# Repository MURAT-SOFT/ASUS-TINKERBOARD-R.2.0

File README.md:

# ASUS-TINKERBOARD-R.2.0
https://learn.microsoft.com/tr-tr/azure/developer/
ASUS TINKERBOARD R.2 AZURE
https://github.com/TinkerBoard-Linux
LINUX KAYNAKLARI
https://www.asus.com/tr/motherboards-components/single-board-computer/all-series/tinker-board/

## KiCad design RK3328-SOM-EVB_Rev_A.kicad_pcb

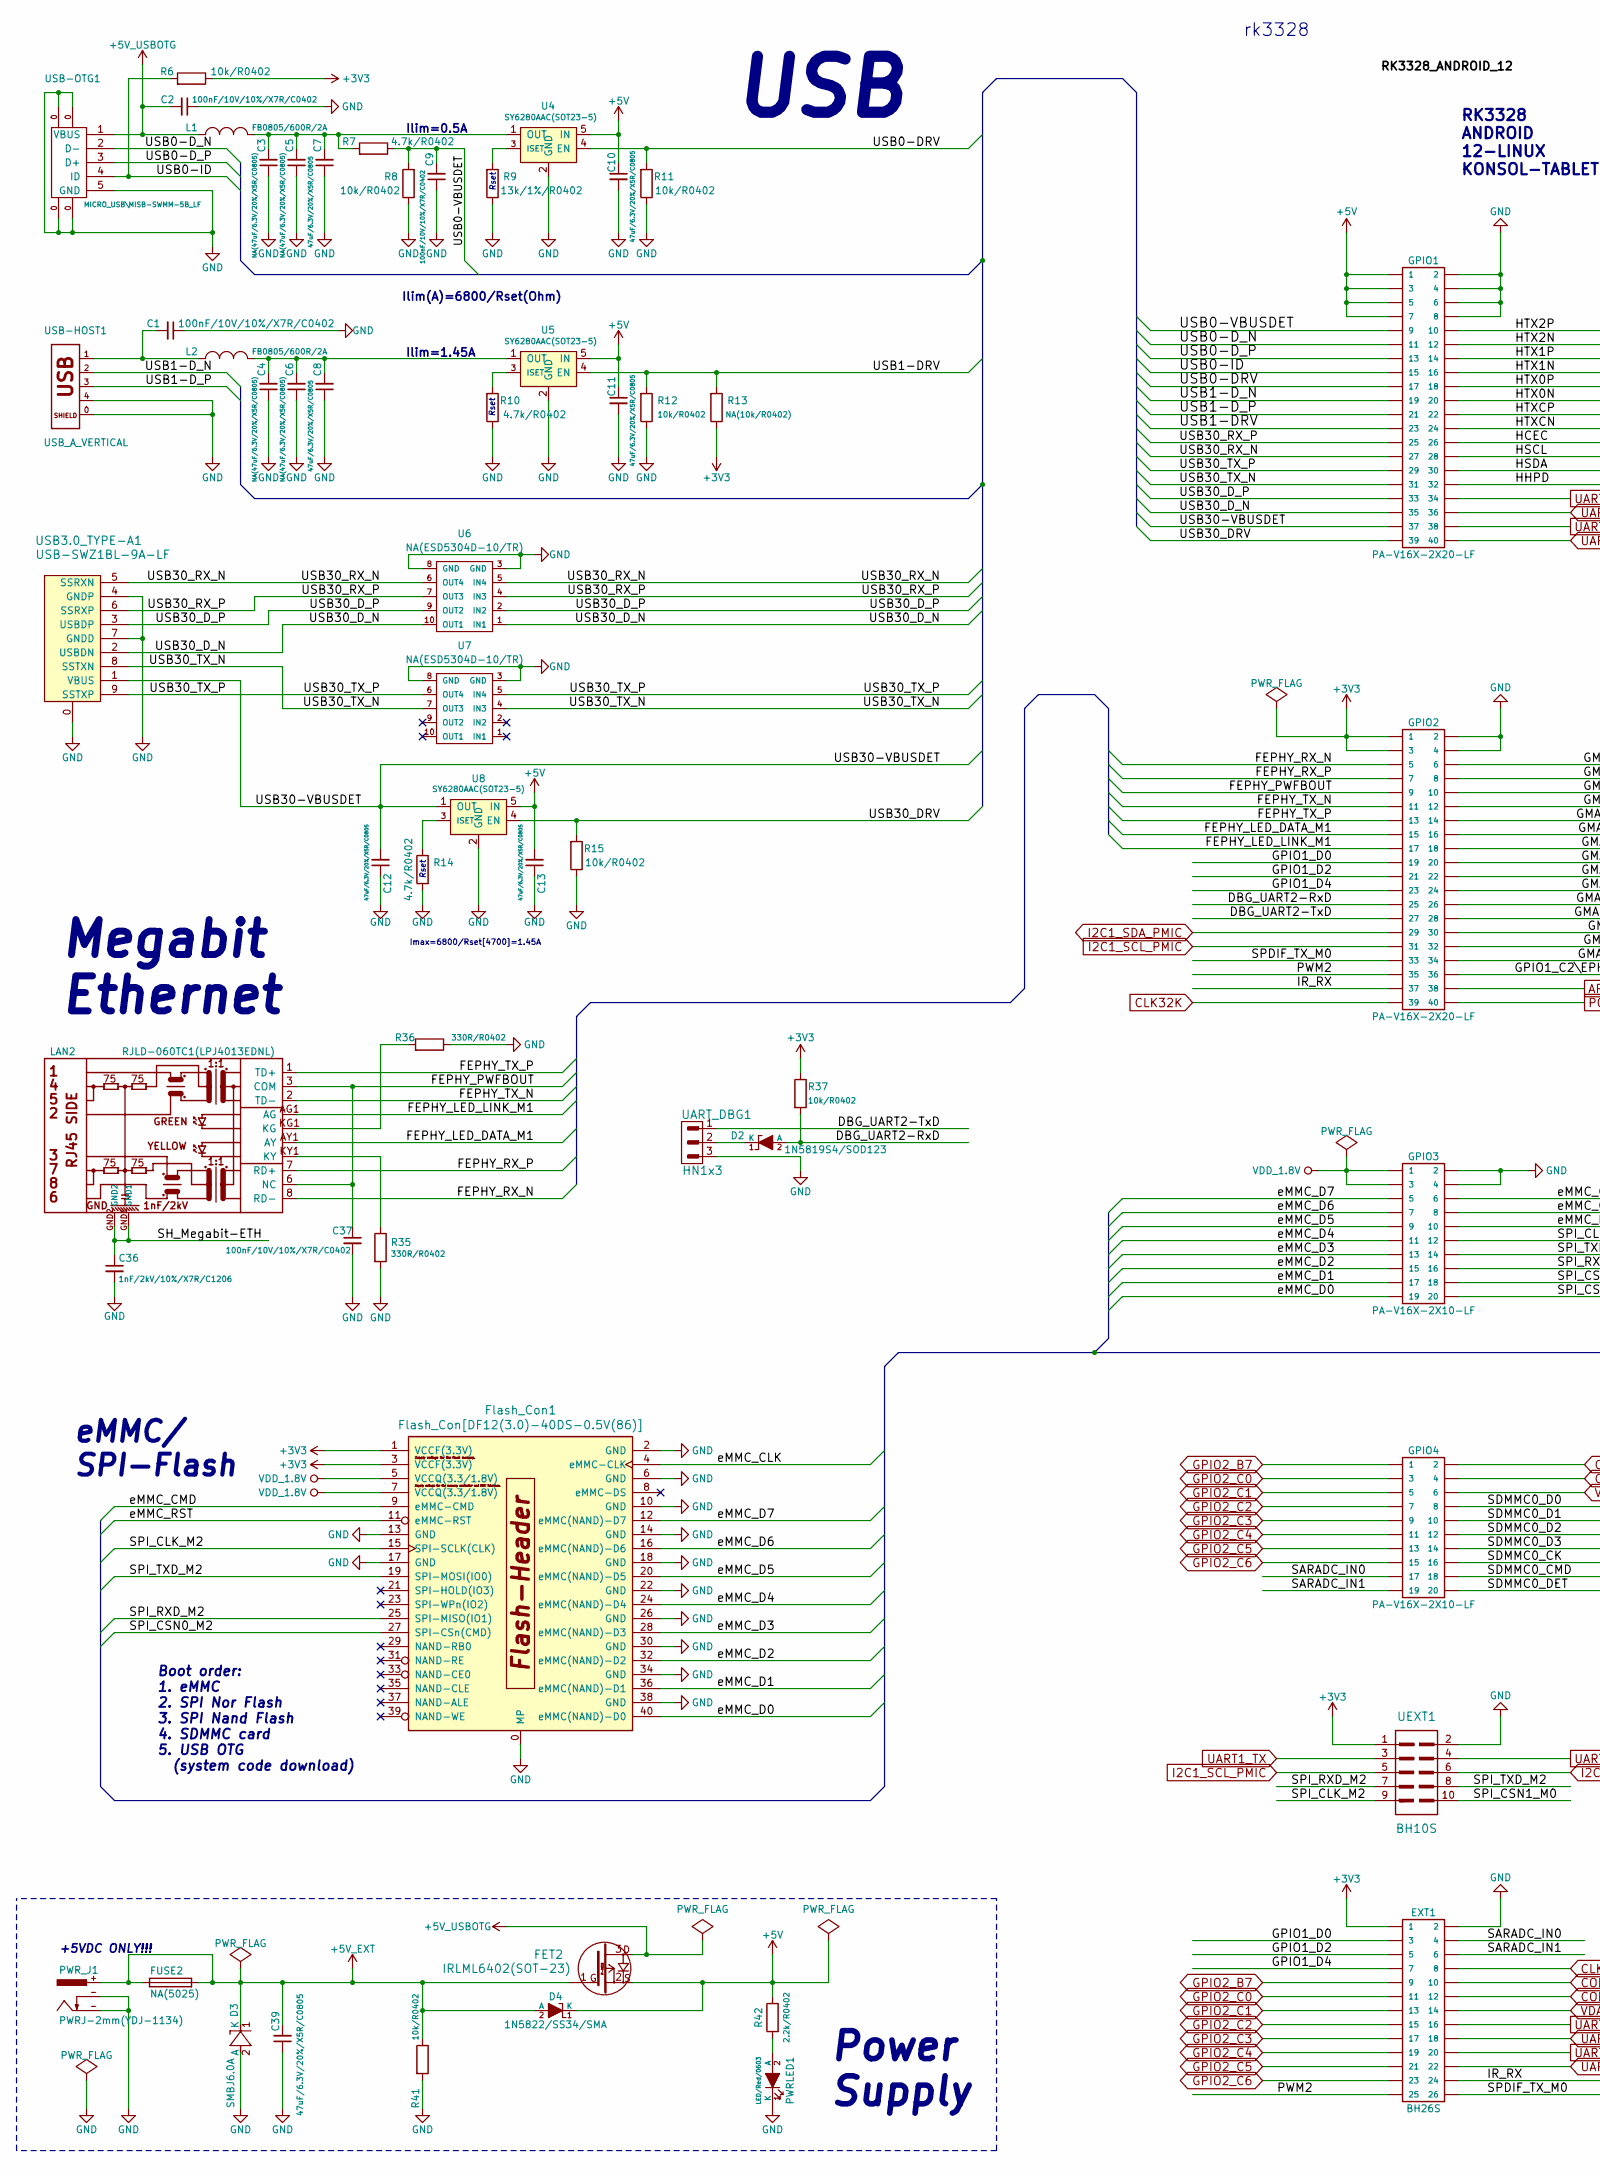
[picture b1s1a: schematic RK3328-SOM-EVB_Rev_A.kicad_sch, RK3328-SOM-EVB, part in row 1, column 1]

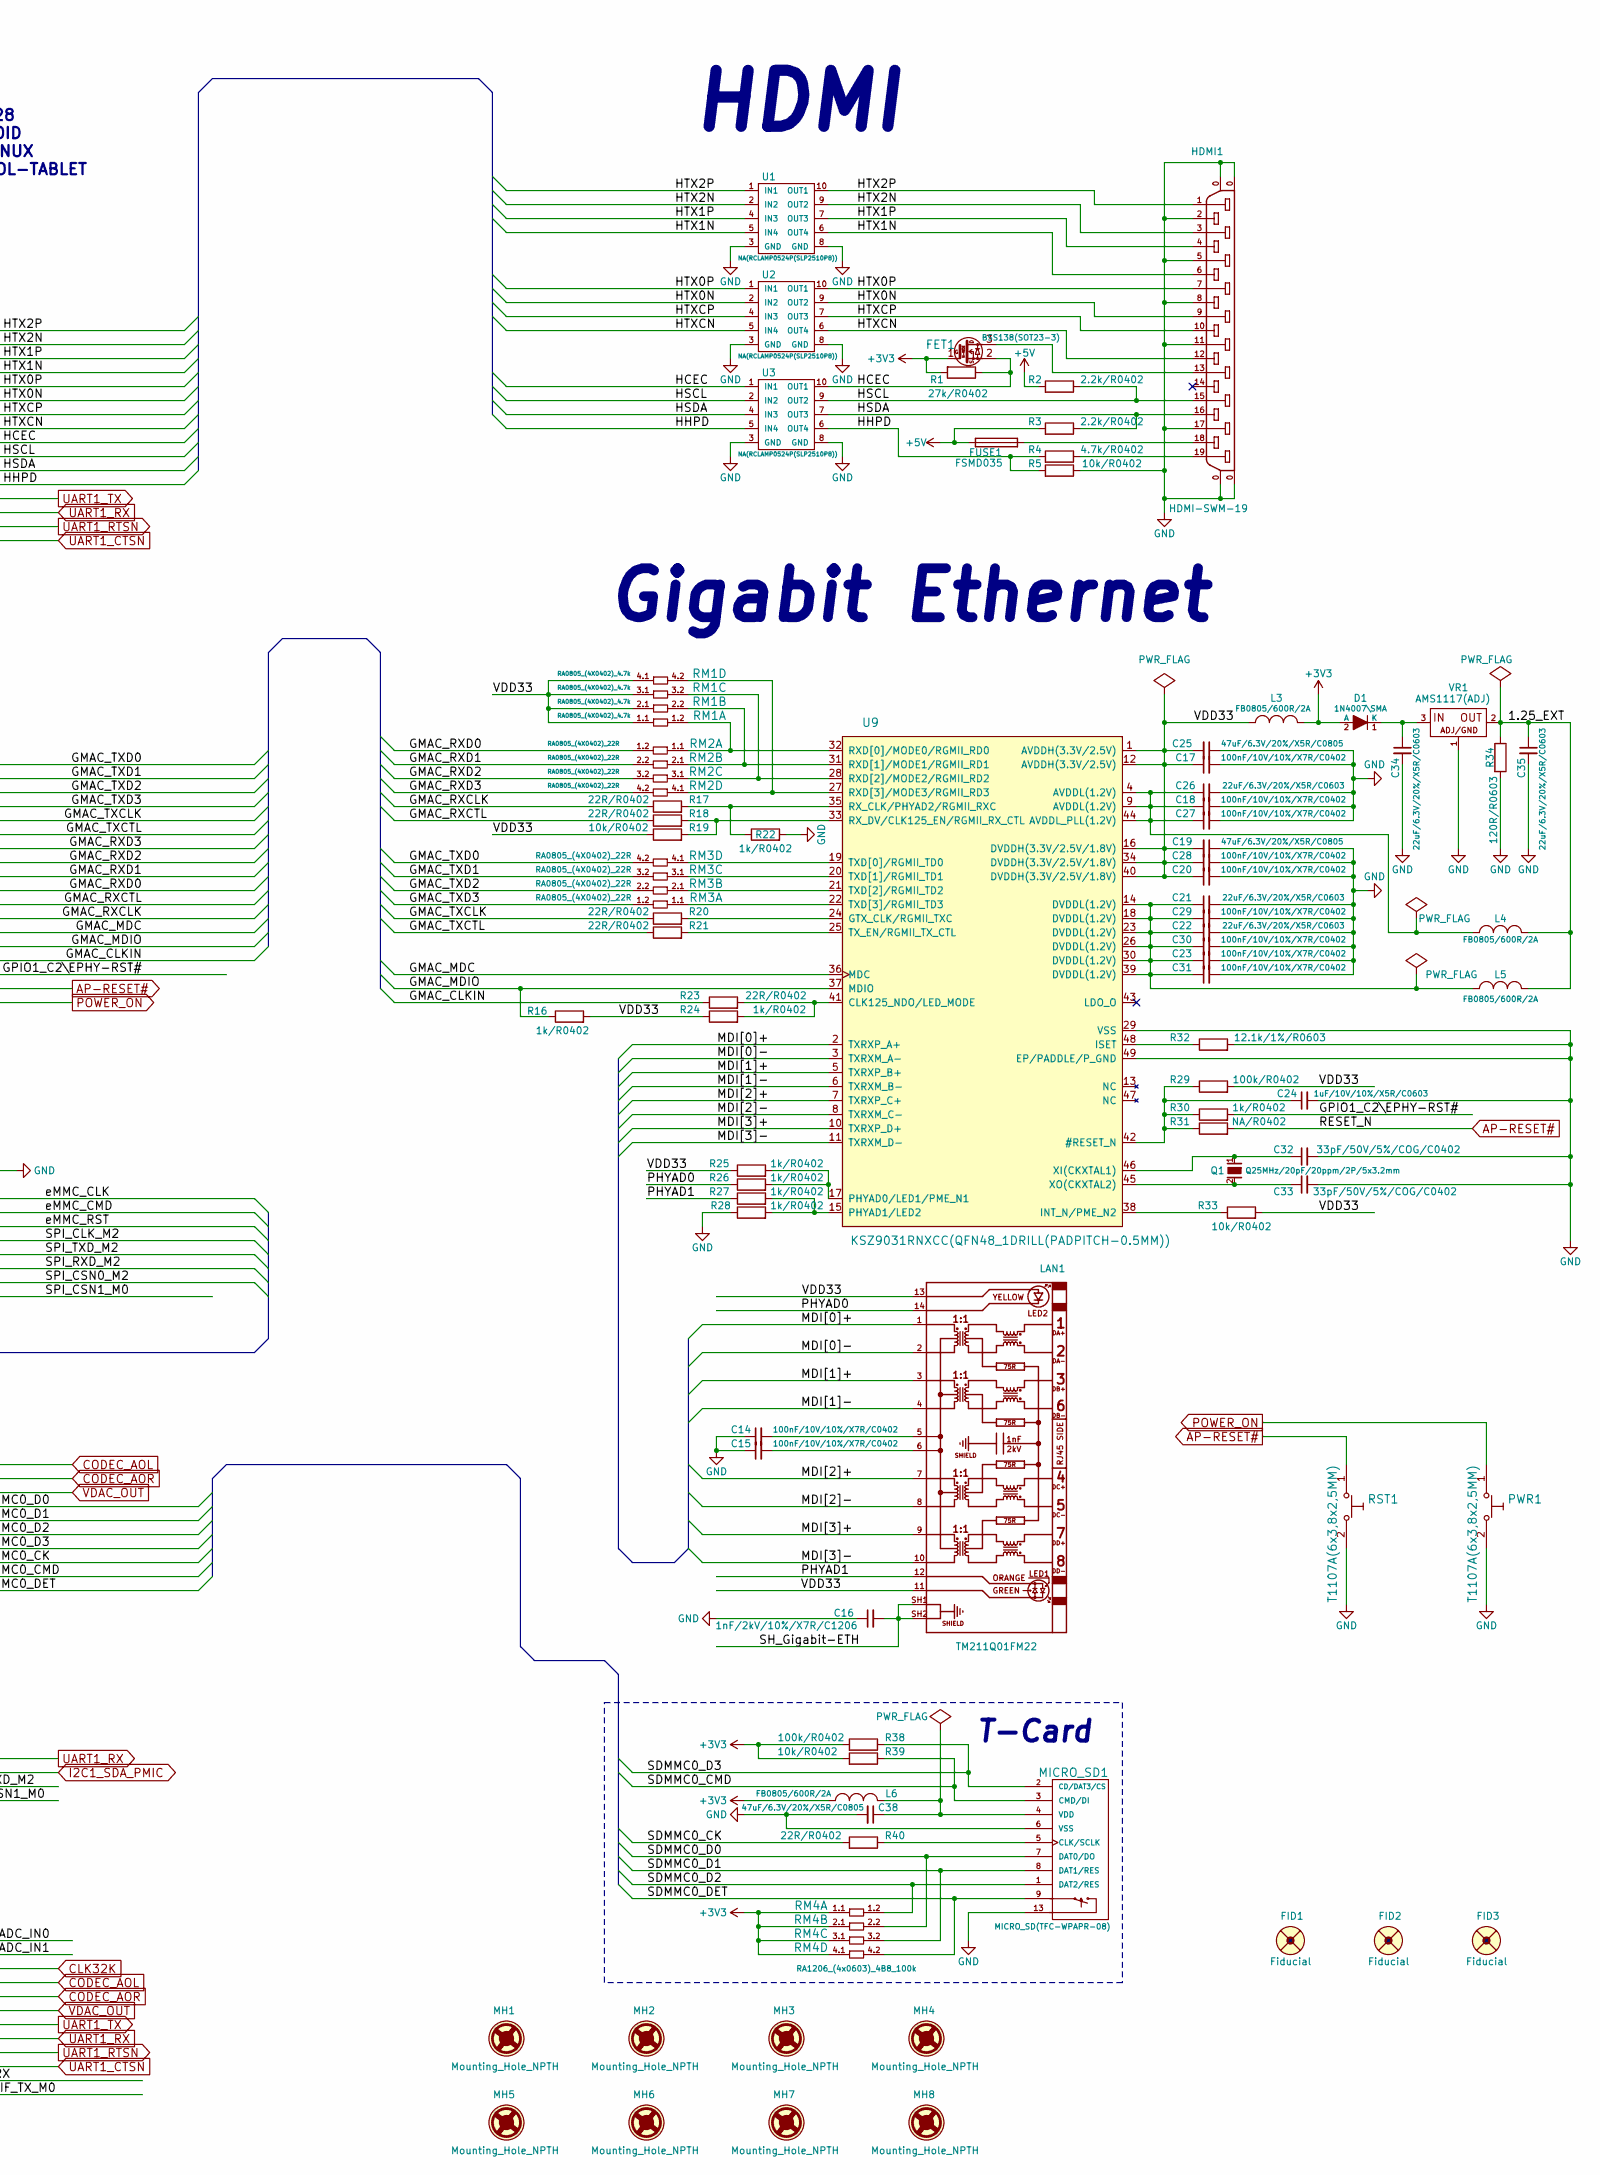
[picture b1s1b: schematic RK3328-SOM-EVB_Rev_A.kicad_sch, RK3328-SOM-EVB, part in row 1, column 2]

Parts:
C1, C2, C9, C14, C15, C17, C18, C20, C23, C27, C28, C29, C30, C31, C37: 100nF/10V/10%/X7R/C0402; C_0402_5MIL_DWS
C3, C4, C5, C6: NA(47uF/6.3V/20%/X5R/C0805); C_0805_5MIL_DWS
C7, C8, C10, C11, C12, C13, C19, C25, C38, C39: 47uF/6.3V/20%/X5R/C0805; C_0805_5MIL_DWS
C16, C36: 1nF/2kV/10%/X7R/C1206; C_1206_5MIL_DWS_ISO
C21, C22, C26, C34, C35: 22uF/6.3V/20%/X5R/C0603; C_0603_5MIL_DWS
C24: 1uF/10V/10%/X5R/C0603; C_0603_5MIL_DWS
C32, C33: 33pF/50V/5%/COG/C0402; C_0402_5MIL_DWS
D1: 1N4007\SMA; SMA-KA
D2: 1N5819S4/SOD123; SOD-123_1C-2A_KA
D3: SMBJ6.0A; DO214AA_1(K)-2(A)
D4: 1N5822/SS34/SMA; SMA-KA
EXT1: BH26S
FET1: BSS138(SOT23-3); SOT23
FET2: IRLML6402(SOT-23); SOT23
FID1, FID2, FID3: Fiducial; Fiducial1x3
FUSE1: FSMD035; FUSE-1206
FUSE2: NA(5025); FUSE-5025
Flash_Con1: Flash_Con[DF12(3.0)-40DS-0.5V(86)]
GPIO1, GPIO2: PA-V16X-2X20-LF; GPH127SMT-02X20(PA-V16X-2X20-LF)
GPIO3, GPIO4: PA-V16X-2X10-LF; GPH127SMT-02X10(PA-V16X-2X10-LF)
HDMI1: HDMI-SWM-19; HDMI-SWM-19-TEST
L1, L2, L3, L4, L5, L6: FB0805/600R/2A; L_0805_5MIL_DWS
LAN1: TM211Q01FM22
LAN2: RJLD-060TC1(LPJ4013EDNL); RJLBC-060TC1
MH1, MH2, MH3, MH4, MH5, MH6, MH7, MH8: Mounting_Hole_NPTH; Mounting_Hole_Drill-3.3mm_Clerance-7mm
MICRO_SD1: MICRO_SD(TFC-WPAPR-08); TFC-WPAPR-08
PWR1: T1107A(6x3,8x2,5MM)
PWRLED1: LED/Red/0603; LED_0603_KA
PWR_J1: PWRJ-2mm(YDJ-1134)
Q1: Q25MHz/20pF/20ppm/2P/5x3.2mm; HCX-4S_2Pins_5.0x3.2mm_TEST
R1: 27k/R0402; R_0402_5MIL_DWS
R2, R3, R42: 2.2k/R0402; R_0402_5MIL_DWS
R4, R7, R10, R14: 4.7k/R0402; R_0402_5MIL_DWS
R5, R6, R8, R11, R12, R15, R19, R33, R37, R39, R41: 10k/R0402; R_0402_5MIL_DWS
R9: 13k/1%/R0402; R_0402_5MIL_DWS
R13: NA(10k/R0402); R_0402_5MIL_DWS
R16, R22, R24, R25, R26, R27, R28, R30: 1k/R0402; R_0402_5MIL_DWS
R17, R18, R20, R21, R23, R40: 22R/R0402; R_0402_5MIL_DWS
R29, R38: 100k/R0402; R_0402_5MIL_DWS
R31: NA/R0402; R_0402_5MIL_DWS
R32: 12.1k/1%/R0603; R_0603_5MIL_DWS
R34: 120R/R0603; R_0603_5MIL_DWS
R35, R36: 330R/R0402; R_0402_5MIL_DWS
RM1: RA0805_(4X0402)_4.7k; RA0805_(4X0402)_xx_BIGGEROUTPADS
RM2, RM3: RA0805_(4X0402)_22R; RA0805_(4X0402)_xx_BIGGEROUTPADS
RM4: RA1206_(4x0603)_4B8_100k; RA1206_(4X0603)_4B8_xx
RST1: T1107A(6x3,8x2,5MM)
U1, U2, U3: NA(RCLAMP0524P(SLP2510P8)); SLP2510P8_TEST
U4, U5, U8: SY6280AAC(SOT23-5); SOT-23-5
U6, U7: NA(ESD5304D-10/TR); SLP2510P8_TEST
U9: KSZ9031RNXCC(QFN48_1DRILL(PADPITCH-0.5MM)); QFN48_1DRILL(PADPITCH-0.5MM)
UART_DBG1: HN1x3
UEXT1: BH10S
USB3.0_TYPE-A1: USB-SWZ1BL-9A-LF; USB3.0-TypeA(USB-SWZ1BL-9A-LF)
USB-HOST1: USB_A_VERTICAL; USB_A_VERTICAL_PTH
USB-OTG1: MICRO_USB\MISB-SWMM-5B_LF; USB-MICRO_MISB-SWMM-5B_LF
VR1: AMS1117(ADJ); SOT223

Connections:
+3V3: D1.2 (A), EXT1.1, FET1.1 (G), Flash_Con1.1 (VCCF(3.3V)), Flash_Con1.3 (VCCF(3.3V)), GPIO2.1, GPIO2.3, L3.2, L6.1, R1.2, R6.1, R13.1, R37.1, R38.2, R39.2, RM4.1.1, RM4.2.1, RM4.3.1, RM4.4.1, UEXT1.1
+5V: C10.1, C11.1, C13.2, D4.1 (K), FET2.2, FUSE1.1, GPIO1.1, GPIO1.3, GPIO1.5, GPIO1.7, R2.2, R3.2, R42.1, U4.5 (IN), U5.5 (IN), U8.5 (IN)
+5V_EXT: C39.2, D3.1 (K), D4.2 (A), FET2.1, FUSE2.1, FUSE2.2, PWR_J1.+, R41.1
+5V_USBOTG: C2.2, FET2.3, L1.1, USB-OTG1.1 (VBUS)
/1.25_EXT: C35.1, L4.2, L5.2, R34.1, VR1.2 (OUT)
/DBG_UART2-RxD: D2.2 (A), GPIO2.25, R37.2
/DBG_UART2-TxD: GPIO2.27, UART_DBG1.1
/FEPHY_LED_DATA_M1: GPIO2.15, LAN2.AY1 (AY)
/FEPHY_LED_LINK_M1: GPIO2.17, LAN2.AG1 (AG)
/FEPHY_PWFBOUT: C37.1, GPIO2.9, LAN2.3 (COM), LAN2.6 (NC)
/FEPHY_RX_N: GPIO2.5, LAN2.8 (RD-)
/FEPHY_RX_P: GPIO2.7, LAN2.7 (RD+)
/FEPHY_TX_N: GPIO2.11, LAN2.2 (TD-)
/FEPHY_TX_P: GPIO2.13, LAN2.1 (TD+)
/GMAC_CLKIN: GPIO2.34, R23.1
/GMAC_MDC: GPIO2.30, U9.36 (MDC)
/GMAC_MDIO: GPIO2.32, R16.1, U9.37 (MDIO)
/GMAC_RXCLK: GPIO2.28, R17.1
/GMAC_RXCTL: GPIO2.26, R18.1
/GMAC_RXD0: GPIO2.24, RM2.1.2
/GMAC_RXD1: GPIO2.22, RM2.2.2
/GMAC_RXD2: GPIO2.20, RM2.3.2
/GMAC_RXD3: GPIO2.18, RM2.4.2
/GMAC_TXCLK: GPIO2.14, R20.1
/GMAC_TXCTL: GPIO2.16, R21.1
/GMAC_TXD0: GPIO2.6, RM3.4.2
/GMAC_TXD1: GPIO2.8, RM3.3.2
/GMAC_TXD2: GPIO2.10, RM3.2.2
/GMAC_TXD3: GPIO2.12, RM3.1.2
/GPIO1_C2\EPHY-RST#: GPIO2.36, R30.2
/GPIO1_D0: EXT1.3, GPIO2.19
/GPIO1_D2: EXT1.5, GPIO2.21
/GPIO1_D4: EXT1.7, GPIO2.23
/HCEC: FET1.2 (S), GPIO1.26, R1.1, U3.1 (IN1), U3.10 (OUT1)
/HHPD: GPIO1.32, R4.2, R5.2, U3.5 (IN4), U3.6 (OUT4)
/HSCL: GPIO1.28, HDMI1.15, R2.1, U3.2 (IN2), U3.9 (OUT2)
/HSDA: GPIO1.30, HDMI1.16, R3.1, U3.4 (IN3), U3.7 (OUT3)
/HTX0N: GPIO1.20, HDMI1.9, U2.2 (IN2), U2.9 (OUT2)
/HTX0P: GPIO1.18, HDMI1.7, U2.1 (IN1), U2.10 (OUT1)
/HTX1N: GPIO1.16, HDMI1.6, U1.5 (IN4), U1.6 (OUT4)
/HTX1P: GPIO1.14, HDMI1.4, U1.4 (IN3), U1.7 (OUT3)
/HTX2N: GPIO1.12, HDMI1.3, U1.2 (IN2), U1.9 (OUT2)
/HTX2P: GPIO1.10, HDMI1.1, U1.1 (IN1), U1.10 (OUT1)
/HTXCN: GPIO1.24, HDMI1.12, U2.5 (IN4), U2.6 (OUT4)
/HTXCP: GPIO1.22, HDMI1.10, U2.4 (IN3), U2.7 (OUT3)
/IR_RX: EXT1.24, GPIO2.37
/MDI[0]+: LAN1.1, U9.2 (TXRXP_A+)
/MDI[0]-: LAN1.2, U9.3 (TXRXM_A-)
/MDI[1]+: LAN1.3, U9.5 (TXRXP_B+)
/MDI[1]-: LAN1.4, U9.6 (TXRXM_B-)
/MDI[2]+: LAN1.7, U9.7 (TXRXP_C+)
/MDI[2]-: LAN1.8, U9.8 (TXRXM_C-)
/MDI[3]+: LAN1.9, U9.10 (TXRXP_D+)
/MDI[3]-: LAN1.10, U9.11 (TXRXM_D-)
/PHYAD0: LAN1.14, R26.1
/PHYAD1: LAN1.12, R27.1
/PWM2: EXT1.25, GPIO2.35
/SARADC_IN0: EXT1.4, GPIO4.17
/SARADC_IN1: EXT1.6, GPIO4.19
/SDMMC0_CK: GPIO4.16, R40.2
/SDMMC0_CMD: GPIO4.18, MICRO_SD1.3 (CMD/DI), R39.1
/SDMMC0_D0: GPIO4.8, MICRO_SD1.7 (DAT0/DO), RM4.2.2
/SDMMC0_D1: GPIO4.10, MICRO_SD1.8 (DAT1/RES), RM4.3.2
/SDMMC0_D2: GPIO4.12, MICRO_SD1.1 (DAT2/RES), RM4.1.2
/SDMMC0_D3: GPIO4.14, MICRO_SD1.2 (CD/DAT3/CS), R38.1
/SDMMC0_DET: GPIO4.20, MICRO_SD1.9, RM4.4.2
/SH_Gigabit-ETH: C16.2, LAN1.SH1, LAN1.SH2
/SH_Megabit-ETH: C36.1, LAN2.GND1, LAN2.GND2
/SPDIF_TX_M0: EXT1.26, GPIO2.33
/SPI_CLK_M2: Flash_Con1.15 (SPI-SCLK(CLK)), GPIO3.12, UEXT1.9
/SPI_CSN0_M2: Flash_Con1.27 (SPI-CSn(CMD)), GPIO3.18
/SPI_CSN1_M0: GPIO3.20, UEXT1.10
/SPI_RXD_M2: Flash_Con1.25 (SPI-MISO(IO1)), GPIO3.16, UEXT1.7
/SPI_TXD_M2: Flash_Con1.19 (SPI-MOSI(IO0)), GPIO3.14, UEXT1.8
/USB0-DRV: GPIO1.17, R11.2, U4.4 (EN)
/USB0-D_N: GPIO1.11, USB-OTG1.2 (D-)
/USB0-D_P: GPIO1.13, USB-OTG1.3 (D+)
/USB0-ID: GPIO1.15, R6.2, USB-OTG1.4 (ID)
/USB0-VBUSDET: C9.2, GPIO1.9, R7.1, R8.2
/USB1-DRV: GPIO1.23, R12.2, R13.2, U5.4 (EN)
/USB1-D_N: GPIO1.19, USB-HOST1.2
/USB1-D_P: GPIO1.21, USB-HOST1.3
/USB30-VBUSDET: C12.2, GPIO1.37, U8.1 (OUT), USB3.0_TYPE-A1.1 (VBUS)
/USB30_DRV: GPIO1.39, R15.2, U8.4 (EN)
/USB30_D_N: GPIO1.35, U6.1 (IN1), U6.10 (OUT1), USB3.0_TYPE-A1.2 (USBDN)
/USB30_D_P: GPIO1.33, U6.2 (IN2), U6.9 (OUT2), USB3.0_TYPE-A1.3 (USBDP)
/USB30_RX_N: GPIO1.27, U6.5 (IN4), U6.6 (OUT4), USB3.0_TYPE-A1.5 (SSRXN)
/USB30_RX_P: GPIO1.25, U6.4 (IN3), U6.7 (OUT3), USB3.0_TYPE-A1.6 (SSRXP)
/USB30_TX_N: GPIO1.31, U7.4 (IN3), U7.7 (OUT3), USB3.0_TYPE-A1.8 (SSTXN)
/USB30_TX_P: GPIO1.29, U7.5 (IN4), U7.6 (OUT4), USB3.0_TYPE-A1.9 (SSTXP)
/VDD33: C17.1, C19.2, C20.1, C25.2, C28.1, L3.1, LAN1.11, LAN1.13, R16.2, R19.1, R24.1, R25.1, R29.2, R33.2, RM1.1.1, RM1.2.1, RM1.3.1, RM1.4.1, U9.1 (AVDDH(3.3V/2.5V)), U9.12 (AVDDH(3.3V/2.5V)), U9.16 (DVDDH(3.3V/2.5V/1.8V)), U9.34 (DVDDH(3.3V/2.5V/1.8V)), U9.40 (DVDDH(3.3V/2.5V/1.8V))
/eMMC_CLK: Flash_Con1.4 (eMMC-CLK), GPIO3.6
/eMMC_CMD: Flash_Con1.9 (eMMC-CMD), GPIO3.8
/eMMC_D0: Flash_Con1.40 (eMMC(NAND)-D0), GPIO3.19
/eMMC_D1: Flash_Con1.36 (eMMC(NAND)-D1), GPIO3.17
/eMMC_D2: Flash_Con1.32 (eMMC(NAND)-D2), GPIO3.15
/eMMC_D3: Flash_Con1.28 (eMMC(NAND)-D3), GPIO3.13
/eMMC_D4: Flash_Con1.24 (eMMC(NAND)-D4), GPIO3.11
/eMMC_D5: Flash_Con1.20 (eMMC(NAND)-D5), GPIO3.9
/eMMC_D6: Flash_Con1.16 (eMMC(NAND)-D6), GPIO3.7
/eMMC_D7: Flash_Con1.12 (eMMC(NAND)-D7), GPIO3.5
/eMMC_RST: Flash_Con1.11 (eMMC-RST), GPIO3.10
AP-RESET#: GPIO2.38, R31.2, RST1.1
CLK32K: EXT1.8, GPIO2.39
CODEC_AOL: EXT1.10, GPIO4.2
CODEC_AOR: EXT1.12, GPIO4.4
GND: C1.1, C2.1, C3.1, C4.1, C5.1, C6.1, C7.1, C8.1, C9.1, C10.2, C11.2, C12.1, C13.1, C14.1, C15.1, C16.1, C17.2, C18.2, C19.1, C20.2, C21.2, C22.2, C23.2, C24.2, C25.1, C26.2, C27.2, C28.2, C29.2, C30.2, C31.2, C32.2, C33.2, C34.2, C35.2, C36.2, C37.2, C38.2, C39.1, D3.2 (A), EXT1.2, Flash_Con1.0 (MP), Flash_Con1.2 (GND), Flash_Con1.6 (GND), Flash_Con1.10 (GND), Flash_Con1.13 (GND), Flash_Con1.14 (GND), Flash_Con1.17 (GND), Flash_Con1.18 (GND), Flash_Con1.22 (GND), Flash_Con1.26 (GND), Flash_Con1.30 (GND), Flash_Con1.34 (GND), Flash_Con1.38 (GND), GPIO1.2, GPIO1.4, GPIO1.6, GPIO1.8, GPIO2.2, GPIO2.4, GPIO3.2, GPIO3.4, HDMI1.0 (20), HDMI1.2, HDMI1.5, HDMI1.8, HDMI1.11, HDMI1.17, MICRO_SD1.6 (VSS), MICRO_SD1.10, MICRO_SD1.11, MICRO_SD1.12, MICRO_SD1.13, PWR1.2, PWRLED1.1 (K), PWR_J1.-, R5.1, R8.1, R9.1, R10.1, R11.1, R12.1, R14.2, R15.1, R22.2, R28.1, R32.2, R34.2, R35.2, R36.1, R41.2, RST1.2, U1.3 (GND), U1.8 (GND), U2.3 (GND), U2.8 (GND), U3.3 (GND), U3.8 (GND), U4.2 (GND), U5.2 (GND), U6.3 (GND), U6.8 (GND), U7.3 (GND), U7.8 (GND), U8.2 (GND), U9.29 (VSS), U9.49 (EP/PADDLE/P_GND), UART_DBG1.3, UEXT1.2, USB3.0_TYPE-A1.0, USB3.0_TYPE-A1.4 (GNDP), USB3.0_TYPE-A1.7 (GNDD), USB-HOST1.0 (5), USB-HOST1.4, USB-OTG1.0, USB-OTG1.5 (GND), VR1.1 (ADJ/GND)
GPIO2_B7: EXT1.9, GPIO4.1
GPIO2_C0: EXT1.11, GPIO4.3
GPIO2_C1: EXT1.13, GPIO4.5
GPIO2_C2: EXT1.15, GPIO4.7
GPIO2_C3: EXT1.17, GPIO4.9
GPIO2_C4: EXT1.19, GPIO4.11
GPIO2_C5: EXT1.21, GPIO4.13
GPIO2_C6: EXT1.23, GPIO4.15
I2C1_SCL_PMIC: GPIO2.31, UEXT1.5
I2C1_SDA_PMIC: GPIO2.29, UEXT1.6
unnamed: C1.2, L2.1, USB-HOST1.1
unnamed: C3.2, C5.2, C7.2, L1.2, R7.2, U4.1 (OUT)
unnamed: C4.2, C6.2, C8.2, L2.2, U5.1 (OUT)
unnamed: C14.2, LAN1.5
unnamed: C15.2, LAN1.6
unnamed: C18.1, C26.1, C27.1, L4.1, U9.4 (AVDDL(1.2V)), U9.9 (AVDDL(1.2V)), U9.44 (AVDDL_PLL(1.2V))
unnamed: C21.1, C22.1, C23.1, C29.1, C30.1, C31.1, L5.1, U9.14 (DVDDL(1.2V)), U9.18 (DVDDL(1.2V)), U9.23 (DVDDL(1.2V)), U9.26 (DVDDL(1.2V)), U9.30 (DVDDL(1.2V)), U9.39 (DVDDL(1.2V))
unnamed: C24.1, R29.1, R30.1, R31.1, U9.42 (#RESET_N)
unnamed: C32.1, Q1.1, U9.46 (XI(CKXTAL1))
unnamed: C33.1, Q1.2, U9.45 (XO(CKXTAL2))
unnamed: C34.1, D1.1 (K), VR1.3 (IN)
unnamed: C38.1, L6.2, MICRO_SD1.4 (VDD)
unnamed: D2.1 (K), UART_DBG1.2
unnamed: FET1.3 (D), HDMI1.13
unnamed: FUSE1.2, HDMI1.18
unnamed: HDMI1.19, R4.1
unnamed: LAN2.KG1 (KG), R36.2
unnamed: LAN2.KY1 (KY), R35.1
unnamed: MICRO_SD1.5 (CLK/SCLK), R40.1
unnamed: PWRLED1.2 (A), R42.2
unnamed: R9.2, U4.3 (ISET)
unnamed: R10.2, U5.3 (ISET)
unnamed: R14.1, U8.3 (ISET)
unnamed: R17.2, R22.1, U9.35 (RX_CLK/PHYAD2/RGMII_RXC)
unnamed: R18.2, R19.2, U9.33 (RX_DV/CLK125_EN/RGMII_RX_CTL)
unnamed: R20.2, U9.24 (GTX_CLK/RGMII_TXC)
unnamed: R21.2, U9.25 (TX_EN/RGMII_TX_CTL)
unnamed: R23.2, R24.2, U9.41 (CLK125_NDO/LED_MODE)
unnamed: R25.2, R26.2, U9.17 (PHYAD0/LED1/PME_N1)
unnamed: R27.2, R28.2, U9.15 (PHYAD1/LED2)
unnamed: R32.1, U9.48 (ISET)
unnamed: R33.1, U9.38 (INT_N/PME_N2)
unnamed: RM1.1.2, RM2.1.1, U9.32 (RXD[0]/MODE0/RGMII_RD0)
unnamed: RM1.2.2, RM2.2.1, U9.31 (RXD[1]/MODE1/RGMII_RD1)
unnamed: RM1.3.2, RM2.3.1, U9.28 (RXD[2]/MODE2/RGMII_RD2)
unnamed: RM1.4.2, RM2.4.1, U9.27 (RXD[3]/MODE3/RGMII_RD3)
unnamed: RM3.1.1, U9.22 (TXD[3]/RGMII_TD3)
unnamed: RM3.2.1, U9.21 (TXD[2]/RGMII_TD2)
unnamed: RM3.3.1, U9.20 (TXD[1]/RGMII_TD1)
unnamed: RM3.4.1, U9.19 (TXD[0]/RGMII_TD0)
POWER_ON: GPIO2.40, PWR1.1
UART1_CTSN: EXT1.22, GPIO1.40
UART1_RTSN: EXT1.20, GPIO1.38
UART1_RX: EXT1.18, GPIO1.36, UEXT1.4
UART1_TX: EXT1.16, GPIO1.34, UEXT1.3
VDAC_OUT: EXT1.14, GPIO4.6
VDD_1.8V: Flash_Con1.5 (VCCQ(3.3/1.8V)), Flash_Con1.7 (VCCQ(3.3/1.8V)), GPIO3.1, GPIO3.3

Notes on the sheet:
RK3328 ANDROID 12-LINUX KONSOL-TABLET
HDMI
Ilim(A)=6800/Rset(Ohm)
+5VDC ONLY!!!
Ilim=1.45A
Power Supply
Gigabit Ethernet
Rset
Megabit Ethernet
rk3328
eMMC/ SPI-Flash
T-Card
Imax=6800/Rset[4700]=1.45A
USB
Boot order: 1. eMMC 2. SPI Nor Flash 3. SPI Nand Flash 4. SDMMC card 5. USB OTG (system code download)
Ilim=0.5A

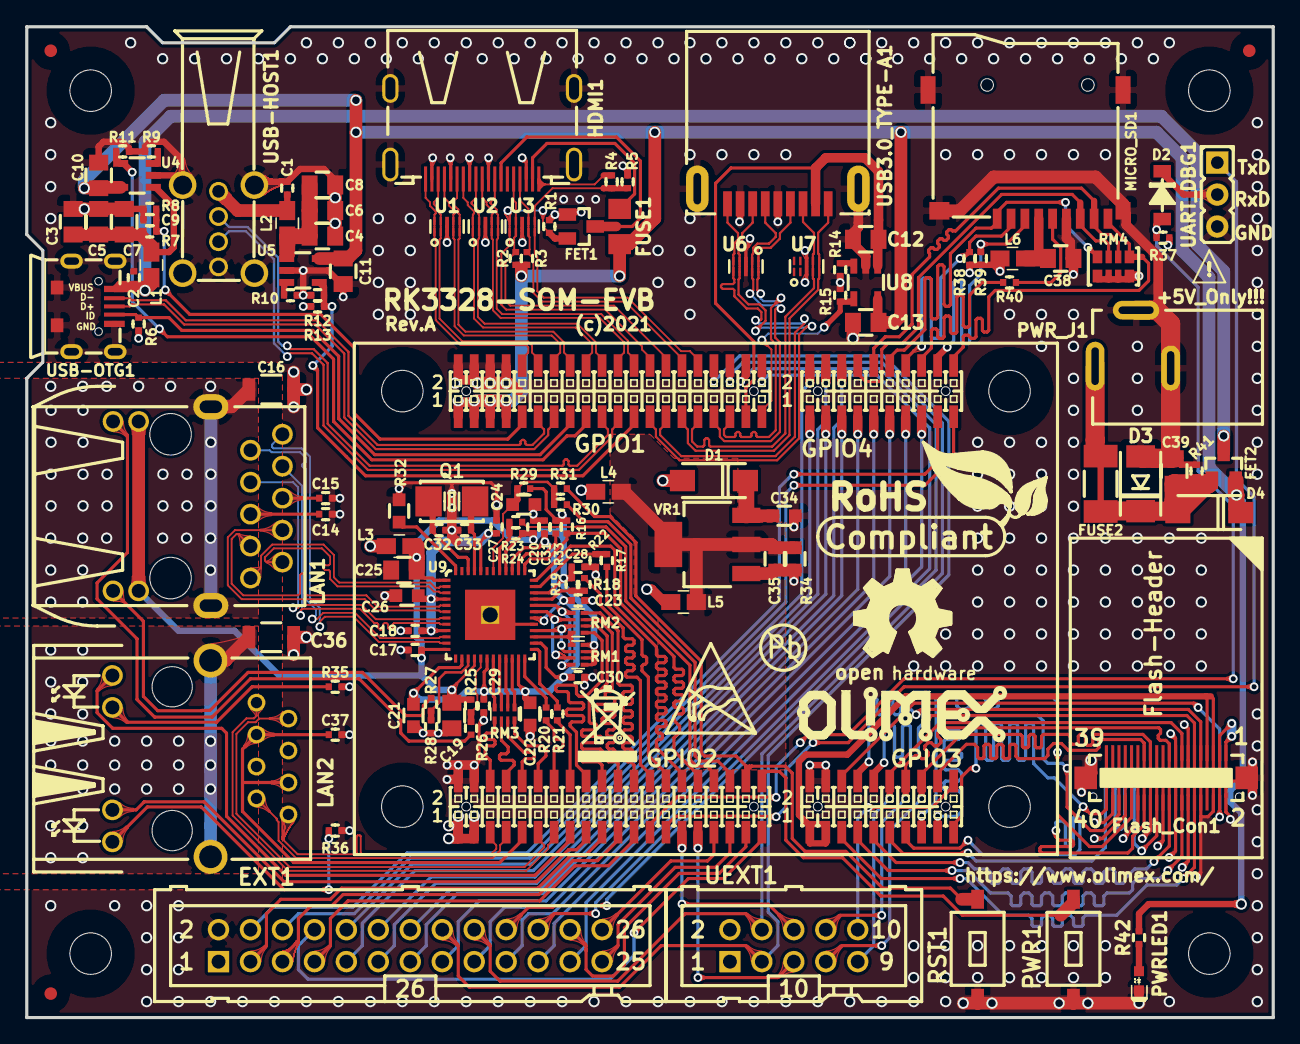
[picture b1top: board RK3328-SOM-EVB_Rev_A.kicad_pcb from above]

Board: 4 copper layers, 99.1 x 78.7 mm, 146 parts (1 on the bottom side), 164 nets.

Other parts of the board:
Olimex logo: OLIMEX_LOGO_TB
Sign_Antistatic: Val**; LOGO_ANTISTATIC_1
Sign_OSHW: LOGO_OPENHARDWARE_8x8
Sign_PB-Free: LOGO_PBFREE
Sign_RecycleBin: LOGO_RECYCLEBIN_1
Sign_RoHS: Val**; LOGO_ROHS_1

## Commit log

2024-11-22 ASUS TINKERBOARD R.2.0
2024-11-23 RK3228 TEKNİK DÖKÜMAN(DATASHEET)
2024-11-23 RK3288 ROCKCHIP TEKNİK DÖKÜMAN(DATASHEET)
    V.2.7 2020
2024-11-23 LPDDR3 BELLEK 2GIGABYTE
2024-11-23 RK808 PMU(GÜÇ YÖNETİM ÜNİTESİ)
2024-11-23 ASUS:TINKERBOARD R.2 SERİ KULLANIM KILAVUZU
2024-11-24 OKU.md
2024-11-24 RK3328 ARM TEK KART BİLGİSAYAR SEMASI
2024-11-24 RK805 GÜC KONTROL UNİTESİ
2024-11-25 RK3328 KICAD PROGRAMI SİSTEM
2024-11-25 SOLIDWORKS 2018 NOTEBOOK
2024-11-25 RK3288 ARM CPU TEKNİK DÖKÜMAN
2024-11-25 BENİ_OKU.md

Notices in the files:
RK3328-SOM-EVB_Rev_A.kicad_pcb:
(c)2021
